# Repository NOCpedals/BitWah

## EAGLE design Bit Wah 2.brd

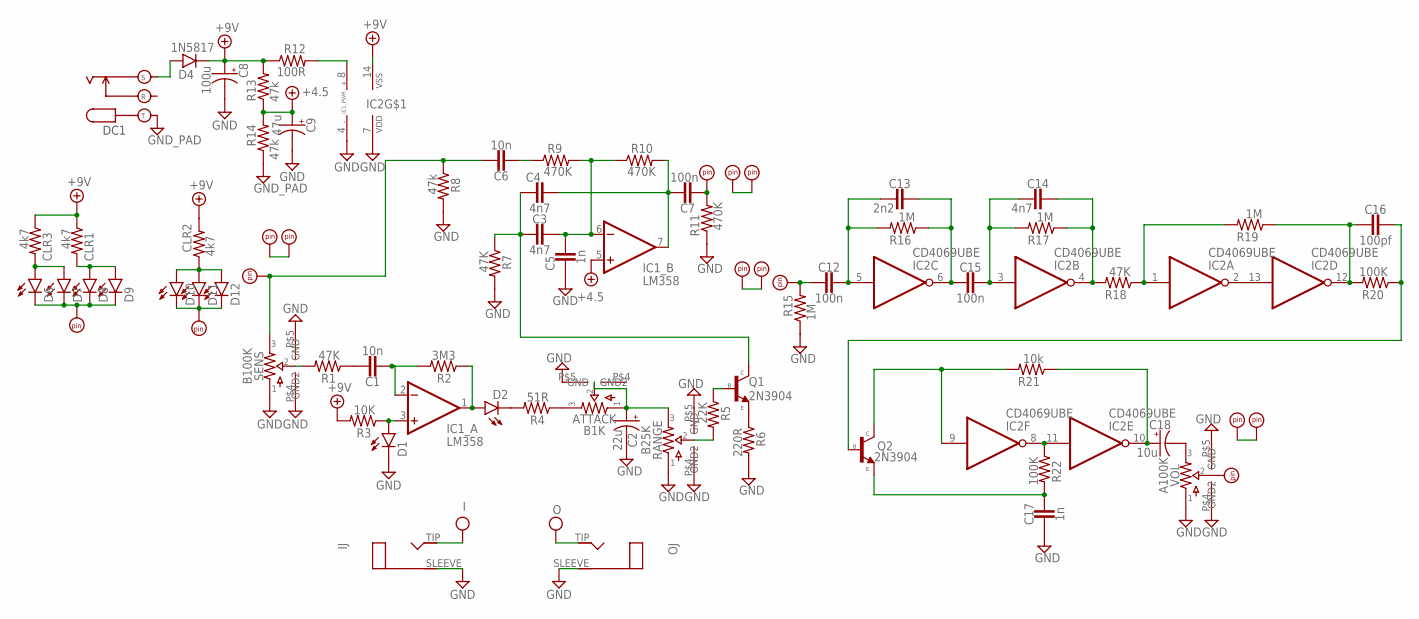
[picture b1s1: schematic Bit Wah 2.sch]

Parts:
1O: PADS.SQR_NL; PAD4
ATTACK: B1K; 9MM_METAL_SHAFT
C1, C6: 10n; 0.2".SML.MED
C2: 22u; 0502
C3, C4, C14: 4n7; 0.2".SML.MED
C5, C17: 1n; 0.2".SML.MED
C7, C12, C15: 100n; 0.2".SML.MED
C8: 100u; 0632
C9: 47u; 0502
C13: 2n2; 0.2".SML.MED
C16: 100pf; 0.2".SML
C18: 10u; 0502
CLR1, CLR2, CLR3: 4k7; R0207/3
D1, D2: 3MM RED; LED3MM
D4: 1N5817; DO41-3
D6, D7, D8, D9, D10, D11, D12: LED3MM
DC1: DC; DC_KOBICONN
GND2, GND5: GND_PAD; SQUARE
I: IN; SQUARE
IC1: LM358; DIP08
IC2: CD4069UBE; DIL14
IJ: MONOPADS; TWO_PADS
O: OUT; SQUARE
OJ: MONOPADS; TWO_PADS
Q1, Q2: 2N3904; INLINE
R1, R7, R18: 47K; R0207/3
R2: 3M3; R0207/3
R3: 10K; R0207/3
R4: 51R; R0207/3
R5: 22K; R0207/3
R6: 220R; R0207/3
R8, R13, R14: 47k; R0207/3
R9, R10, R11: 470K; R0207/3
R12: 100R; R0207/3
R15, R16, R17, R19: 1M; R0207/3
R20, R22: 100K; R0207/3
R21: 10k; R0207/3
RA: PADS.SQR_NL; PAD4
RANGE: B25K; 9MM_METAL_SHAFT
RB, RB1: PADS.SQR_NL; PAD4
SA, SA1: PADS.SQR_NL; PAD4
SB, SB1: PADS.SQR_NL; PAD4
SENS: B100K; 9MM_METAL_SHAFT
SW1: SW1; PAD4
SW2: PADS.SQR_NL; PAD4
U$4: OUT1; PAD4
U$5, U$6, U$7: PADS.SQR_NL; PAD4
VOL: A100K; 9MM_METAL_SHAFT

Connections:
+9V: C8.+, CLR1.1, CLR2.2, CLR3.1, D4.C, IC2.14 (VSS), R3.2, R12.1, R13.2
GND: ATTACK.P$5 (GND2), C2.-, C5.2, C8.-, C9.-, C17.2, D1.K (C), DC1.T, GND2.1, GND5.1, IC1.4 (V-), IC2.7 (VDD), IJ.SLEEVE, OJ.SLEEVE, R6.2, R7.2, R8.2, R11.1, R14.1, R15.1, RANGE.P$1 (1), RANGE.P$4 (GND), RANGE.P$5 (GND2), SENS.P$1 (1), SENS.P$4 (GND), SENS.P$5 (GND2), VOL.P$1 (1), VOL.P$4 (GND), VOL.P$5 (GND2)
IN: I.1, IJ.TIP
unnamed: C1.1, R1.1
unnamed: 1O.P$1, RA.P$1
unnamed: D1.A, IC1.3 (+IN), R3.1
unnamed: D4.A, DC1.S
unnamed: ATTACK.P$1 (1), ATTACK.P$2 (2), C2.+, RANGE.P$3 (3)
unnamed: SA.P$1, SA1.P$1
unnamed: R1.2, SENS.P$2 (2)
unnamed: C1.2, IC1.2 (-IN), R2.2
unnamed: D2.A, IC1.1 (OUT), R2.1
unnamed: D2.K (C), R4.2
unnamed: ATTACK.P$3 (3), R4.1
unnamed: IC1.8 (V+), R12.2
unnamed: Q1.1 (E), R6.1
unnamed: R5.2, RANGE.P$2 (2)
unnamed: Q1.2 (B), R5.1
unnamed: C3.2, C4.2, Q1.3 (C), R7.1
unnamed: C3.1, C5.1, IC1.6 (-IN), R9.2, R10.1
unnamed: C6.2, R9.1
unnamed: C12.1, C13.2, IC2.5 (I), R16.2
unnamed: C4.1, C7.1, IC1.7 (OUT), R10.2
unnamed: C13.1, C15.2, IC2.6 (O), R16.1
unnamed: C14.2, C15.1, IC2.3 (I), R17.2
unnamed: C14.1, IC2.4 (O), R17.1, R18.2
unnamed: IC2.1 (I), R18.1, R19.2
unnamed: IC2.2 (O), IC2.13 (I)
unnamed: C16.2, IC2.12 (O), R19.1, R20.2
unnamed: C16.1, Q2.2 (B), R20.1
unnamed: IC2.8 (O), IC2.11 (I), R22.1
unnamed: C17.1, Q2.1 (E), R22.2
unnamed: C18.+, IC2.10 (O), R21.1
unnamed: C18.-, VOL.P$3 (3)
unnamed: IC2.9 (I), Q2.3 (C), R21.2
unnamed: D6.K (C), D7.K (C), D8.K (C), D9.K (C), SW1.P$1
unnamed: D10.K (C), D11.K (C), D12.K (C), SW2.P$1
unnamed: CLR1.2, D8.A, D9.A
unnamed: CLR2.1, D10.A, D11.A, D12.A
unnamed: SB.P$1, SB1.P$1
unnamed: RB.P$1, RB1.P$1
unnamed: C7.2, R11.2, U$4.P$1
unnamed: C6.1, R8.1, SENS.P$3 (3), U$5.P$1
unnamed: C12.2, R15.2, U$6.P$1
unnamed: U$7.P$1, VOL.P$2 (2)
unnamed: CLR3.2, D6.A, D7.A
OUT: O.1, OJ.TIP
VA: C9.+, IC1.5 (+IN), R13.1, R14.2

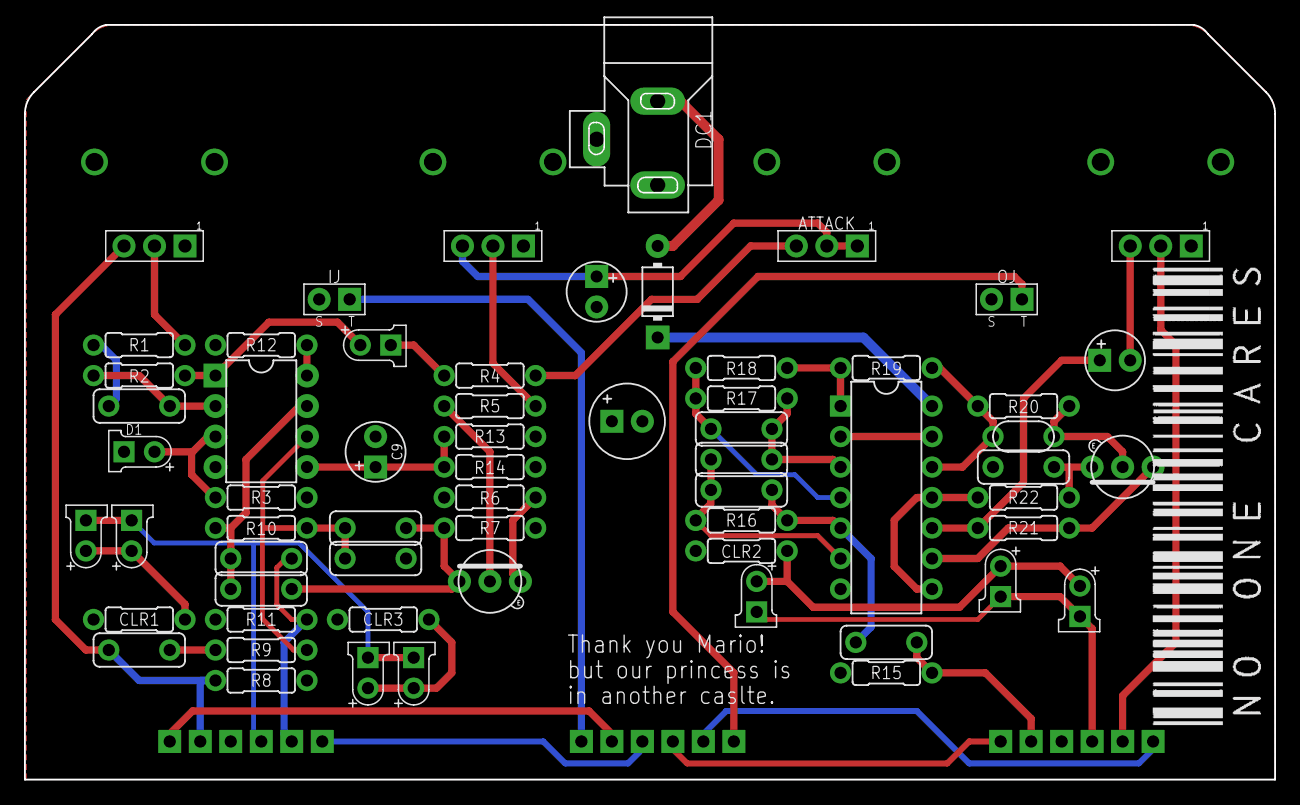
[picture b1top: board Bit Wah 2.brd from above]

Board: 2 copper layers, 104.1 x 62.9 mm, 80 parts (0 on the bottom side), 48 nets.
